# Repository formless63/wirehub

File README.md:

# WireHub

Capture the cable assemblies you build as one canonical definition, and get everything else
derived from it: schematic, build sheet, BOM, continuity spec and drawing. Self-hosted,
free software, deterministic output.

<p align="center">
  <picture>
    <source media="(prefers-color-scheme: dark)" srcset="docs/assets/hero-dark.webp">
    
  </picture>
</p>

<p align="center">
  <b><a href="https://formless63.github.io/wirehub/docs/">Documentation</a></b> ·
  <a href="https://formless63.github.io/wirehub/docs/quick-start/">Quick start</a> ·
  <a href="https://formless63.github.io/wirehub/generator/">Config generator</a> ·
  <a href="https://formless63.github.io/wirehub/store/">Module store</a>
</p>

## See it work

From a new design to a build sheet, about twenty seconds: the wizard wires what the catalog
states unambiguously, the canvas lets you change any joint, and every document follows.

## What you get

Every document is derived from the one definition, so they always agree.

<table>
  <tr>
    <td width="25%" valign="top"><br><sub><b>Schematic</b><br>laid out for you, with a legend and cross-section</sub></td>
    <td width="25%" valign="top"><br><sub><b>Build sheet</b><br>the bench flow, one stage per step</sub></td>
    <td width="25%" valign="top"><br><sub><b>Continuity spec</b><br>what must connect, what must stay isolated</sub></td>
    <td width="25%" valign="top"><br><sub><b>Drawing sheet</b><br>BOM, outline and title block on a framed sheet</sub></td>
  </tr>
</table>

Plus a BOM, formboard, wire labels, CSV and XLSX exports, and WireViz import and export.

## What is in it

- **A hierarchical wire model.** A stock is a tree: cables hold pairs, coax and cores,
  which hold conductors, shields and insulation. Bonded screens, drains, pigtails and
  breakouts (moulds where some conductors pass through and others end) are modelled
  as they are built.
- **A connector library.** A connector is a physical body (DE-9 male, XLR3 female)
  composed with a pinout (RS-232, balanced audio). Reuse one body for many pinouts.
- **PCBAs as black boxes** with declared internal continuity, so a trace runs through a
  board without modelling its electronics.
- **Derived, deterministic output.** Nets and traces, a continuity spec, a BOM, a
  bench build sheet, an ELK-laid-out SVG schematic and an ANSI-A drawing sheet all come
  from the same JSON definition, byte for byte the same every time.
- **An editor.** A React canvas for the wiring, a parts library with 3D views, a new-cable
  wizard, versions, edit locks and an optional login.
- **Modules.** Domain vocabularies (video, audio, fieldbus …) and what only one shop needs
  (its ERP link, its numbering scheme, its own importers) plug in at build time through
  a small registry instead of living in the base.

## Run it

You need Docker and one file — no clone, no `.env`:

```
mkdir wirehub && cd wirehub
curl -fsSLO https://raw.githubusercontent.com/formless63/wirehub/main/compose.yaml
docker compose up -d
docker compose logs wirehub        # the first-run setup code
```

Open <http://localhost:5183/setup>, enter the setup code and finish the short form; you land on a list of example designs to open. In a Docker UI
(Portainer, Komodo, Dockhand …), paste
[`compose.yaml`](https://raw.githubusercontent.com/formless63/wirehub/main/compose.yaml)
as a stack, deploy, and read the code from the `wirehub` container's logs.

On first start a one-shot `bootstrap` service generates every secret the stack
needs into a `secrets` volume and keeps it there. The few install choices — the
public URL, ports, backups (`COMPOSE_PROFILES=backup`), your own PostgreSQL or
S3 — go in an optional `.env`;
[`.env.example`](https://raw.githubusercontent.com/formless63/wirehub/main/.env.example)
explains each. Everything else — single sign-on, magic links, allowed emails,
alerts, the git mirror, job settings — is set in the app under **Settings** and
applies without a redeploy.

**Config generator: <https://formless63.github.io/wirehub/generator/>** — pick your
options and get a ready `compose.yaml` and `.env`. It runs entirely in your
browser and sends nothing anywhere.

**First-run setup** lists the bundled domain modules whose signals, connectors
and example cables you can add — **PC & serial** (RS-232, RS-485, USB),
**Networking** (RJ45, T568A/B), **Pro audio** (XLR, TRS, RCA), **AV / video** and
**Automotive** — all unticked unless the deployment suggests some. Nothing is
required, and more can be enabled later from the command palette. The base
itself stays generic: its starter catalog holds wire stocks, generic connectors
(DE-9 by pin number, JST XH, terminal blocks), parts and a few neutral example
cables.

The stack is the app, PostgreSQL 18 and [Garage](https://garagehq.deuxfleurs.fr/)
(S3-compatible storage for uploaded files), plus restic backups through
Backrest as an optional profile. `docs/self-hosting.md` has the details.

## Develop

From source (Node 24+, pnpm 10 — `corepack enable`):

```
git clone https://github.com/formless63/wirehub && cd wirehub
pnpm install
pnpm --filter studio dev        # open the printed URL
```

The hub opens on the generic starter catalog: a few example cables built from a
small library of generic parts, every value cited to a public standard or marked
as a synthetic example. The catalog is plain JSON under `packages/catalog/data`,
and saves go straight back to it; domain modules enabled at setup install their
packs into the gitignored `data/packs/`, so they never land in a commit to the
base.

```
pnpm build                      # tsc --noEmit, strict, every package
pnpm test                       # vitest, each workspace in turn
pnpm --filter @wirehub/model test -- test/trace.test.ts
bash scripts/privacy-check.sh --tree
```

`pnpm install` also enables git hooks that keep home paths, secrets and personal
emails out of commits (`CONTRIBUTING.md`).

| Package | |
| --- | --- |
| `@wirehub/model` | the canonical model: types, validation, nets, trace, part-number schemes. Zero dependencies. |
| `@wirehub/catalog` | the file-backed catalog and the starter data. Zero dependencies. |
| `@wirehub/modules` | the module API and build-time registry. Zero dependencies, MIT. |
| `@wirehub/layout` | ELK layout of a design |
| `@wirehub/render-svg` | deterministic SVG schematics and cross-sections |
| `@wirehub/docs` | build sheet, BOM, continuity spec, drawing, wire spec |
| `@wirehub/editor-react` | the editor |
| `apps/studio` | the app: Vite SPA and Hono server; `stack/` the compose stack's one-shots |
| `site` | the config generator, published to GitHub Pages |
| `modules/*` | bundled modules: optional domain modules (`pc-serial`, `networking`, `pro-audio`, `av-video`, `automotive`) and the always-on interop modules `wireviz` (WireViz YAML in and out) and `csv-library` (bulk CSV library import) |

## Read next

- **Documentation: <https://formless63.github.io/wirehub/docs/>** — quick start, your first design, concepts, and the reference below.
- `SPEC.md` — the model and the plan; the single source of truth.
- `docs/modules.md` — extension points, domain modules, and how a private module lives
  in its own repository.
- `docs/exports.md` — CSV/XLSX exports, the continuity tester export, wire labels, and rendering documents without a browser.
- `docs/interop.md` — WireViz YAML import and export, bulk CSV library import, and part costing.
- `docs/catalog-store.md` — catalog packs: format, provenance, install and update.
- `docs/store-hosting.md` — run your own module store from a GitHub template (or any static host).
- `docs/self-hosting.md` — install, the compose stack, secrets, storage, backups, development.
- `specs/postgres-backend.md` — the database backend (Phase A built).
- `docs/boundaries.md` — what this base was split from, and what it left out.

Contributing: `CONTRIBUTING.md` · Security: `SECURITY.md` · Conduct: `CODE_OF_CONDUCT.md`

## Licence

WireHub is free software under the **GNU Affero General Public License v3.0 only**
(`LICENSE`), with one additional permission, the **WireHub Module Exception**
(`MODULE-EXCEPTION.md`). In plain language:

- **WireHub itself stays open.** If you modify WireHub and run it for others — including
  over a network — you offer them the source of your modified WireHub, under the AGPL.
- **Modules can use any licence.** A module that talks to WireHub only through the module
  API (`@wirehub/modules`, the model and catalog types) and the catalog-pack formats may
  be MIT, proprietary, or anything else. You can build and distribute a WireHub image that
  includes it without the module becoming AGPL, and without publishing its source.
- **`@wirehub/modules` is MIT**, so module authors can depend on it freely.
- **Catalog data is CC0-1.0.** The starter catalog (`packages/catalog/data`) and the
  bundled modules' packs are dedicated to the public domain, so the facts in them can
  be reused anywhere. Other packs, and records in them, carry their own licence
  (`docs/catalog-store.md`).
- Third-party material keeps its own licence (`NOTICE`).

There are no per-file licence headers: `LICENSE`, `MODULE-EXCEPTION.md` and each
package's `license` field are the record (`SPDX: AGPL-3.0-only WITH
AdditionRef-WireHub-Module-Exception-1.0`, `packages/modules`: `MIT`; `packages/catalog`: `AGPL-3.0-only AND CC0-1.0`, the code and
its data; bundled modules: `MIT`, their packs `CC0-1.0`). This summary is
not legal advice; the licence texts govern.

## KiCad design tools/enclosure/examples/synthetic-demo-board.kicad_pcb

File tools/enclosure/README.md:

# Tool pack: enclosure

Parametric board enclosures with [build123d](https://github.com/gumyr/build123d) 0.13.0 on
Open CASCADE (OCP 8.0.1). Image `wirehub-tool-enclosure:0.3.5`; pins in `Dockerfile` and
`requirements.lock` (hash-checked, `uv pip compile requirements.in --generate-hashes`).

```sh
docker build -t wirehub-tool-enclosure:0.3.5 tools/enclosure
docker run --rm --network none --read-only --tmpfs /tmp \
  -v "$IN":/work/in:ro -v "$OUT":/work/out \
  wirehub-tool-enclosure:0.3.5 enclosure-generate /work/in/request.json
```

Same request, same bytes (0.3.3+): every STEP gets a fixed `FILE_NAME` stamp and a canonical
entity numbering (`repro.py`, the same file as `tools/kicad/repro.py`), and `result.json` /
`device-result.json` carry no timings (the run time is in `log.txt`).

## Op `enclosure-generate`

`request.json` → `params`:

- `boards[]`: `{ id, label, basis, thickness, outline: [[x, y], …], holes: [{ x, y, d }],
  components: [{ ref, x0, y0, x1, y1, height | null, basis?, side }], ports: [{ id, label, edge:
  front|back|left|right, at, z, width, height, shape: rect|round, protrude }], heightAbove,
  heightBelow }`. Board-local millimetres, **y toward the back**, origin at the outline's
  bounding-box minimum, underside at z = 0. `height: null` is an unknown height: it is modelled at
  `defaultComponentHeight` and reported, never treated as zero. A component whose `basis` is
  `estimated` (the studio read it from the footprint's name, not a 3D model) is reported as such
  and its collisions say so.
- `occurrences[]`: `{ id, board, x?, y?, rotation? }`. The same board may appear more than once;
  occurrences without `x`/`y` are laid out left to right.
- `enclosure`: design parameters (wall, floor, lid thickness, clearance, standoff height and
  diameter, pilot, lid `flat` with screw posts or `split` at a height, lip and fit, vents). All have
  defaults (`DEFAULTS` in `enclosure.py`).
- `openings[]`: extra cut-outs in the enclosure frame (`face`, `u`, `v`, `width`, `height`, `shape`).

Outputs (manifest roles): `base-step`, `lid-step`, `base-stl`, `lid-stl` (flipped plate-down for
printing), `assembly-step` (base, lid and board dummies), `preview-model` (`assembly.glb`, millimetres like the Library's own GLBs,
lid lifted), `preview-image` (`preview.png`, a z-buffered isometric render made without GL) and
`result` (`result.json`: outer/interior size, each occurrence's placement matrix, resolved
openings, supports, lid posts, volumes, the effective parameters). Each `supports[]` entry is
`{ occurrence, kind: board-hole | corner-pad, x, y, z }` (z = the support's top, the board's
underside; a `board-hole` also gives `holeDiameter`, `standoffDiameter`, `pilotDiameter`, a
`corner-pad` its `size`); each `lidPosts[]` entry is a flat lid's screw axis `{ x, y, size, z0, z1,
pilotDiameter, pilotDepth, screwZ }` (screwZ = the lid's outside), empty without lid screws.
Consumers read these instead of re-deriving them from the parameters.

Findings are advisory: unknown heights, ports set back from a wall, collisions between the
shell/lid and declared board geometry (boolean intersection, as in the reference generator),
missing mounting holes. Invalid parameters give `status: "failed"` with an `error` finding; the
process still exits 0. Running without `--user`, the pack hands its outputs to the owner of
`/work/out`.

Examples (synthetic and public-safe, made up for this pack): `examples/synthetic-two-boards.json`
is a request with one board placed twice; `examples/synthetic-demo-board.kicad_pcb` is a 60 × 40 mm
KiCad board built from KiCad's standard footprints by `examples/make-synthetic-board.py` (run with
KiCad's Python). Uploaded as a board's model in the Library, it gives an enclosure a native outline,
four mounting holes and two edge connectors.

In the app: a board's record → Enclosures → New enclosure creates a shell carrying the parameters;
its Enclosure panel saves them and runs Generate (`POST /api/enclosures/:id/generate`), an
`enclosure-generate` job run by the shared tool-pack runner where `WIREHUB_TOOL_RUNNER=docker` is set
(progress and Cancel in the panel; `docs/jobs-and-tool-packs.md`).

## Op `device-assemble` (pack 0.3.0)

A whole device in one run: `assemble.py` (the image's `entry.py` sends this op there). The studio
composes the device (`deviceScene` in `@wirehub/model`) and passes every placed thing as a part:
`{ path, kind, label, group?, matrix (4×4, device frame, mm, z up), provisional?, geometry }`, where
`geometry` is a STEP input (`frame: board` moves a KiCad board STEP so its PCB body's outline minimum
is the origin and its underside z = 0), a board outline with footprint boxes, a box, parametric
hardware (`screw`, `standoff`, `foot`) or a cable route tube. `params.drawing` fills the title block
and parts list (a long title wraps to two lines, then ends in an ellipsis; an unsaved-version export reads `unreleased`); `false` skips the sheet.

Outputs: `device-step` (device.step, one named, coloured node per part, grouped by sub-assembly),
`device-glb` (millimetres, y up), `preview-image`, `device-drawing` (an A3 SVG: front, top and right
views in third-angle projection with hidden lines, an isometric view, overall dimensions, parts list
and title block; lid screws and feet in a table with their pitch dimensioned), `device-drawing-pdf`
(that sheet plus one per nested sub-device, in its own frame with its own parts list: a multi-page
PDF; pack 0.3.3) and `result` (bounding box, each part's geometry and status, the sheet's scale).
Cable routes are in the STEP and GLB but not on the drawing: they are schematic. In the app: a
design's Device view → Exports (`POST /api/devices/:id/exports`, a `device-export` job), from the
working copy or the saved version being viewed.

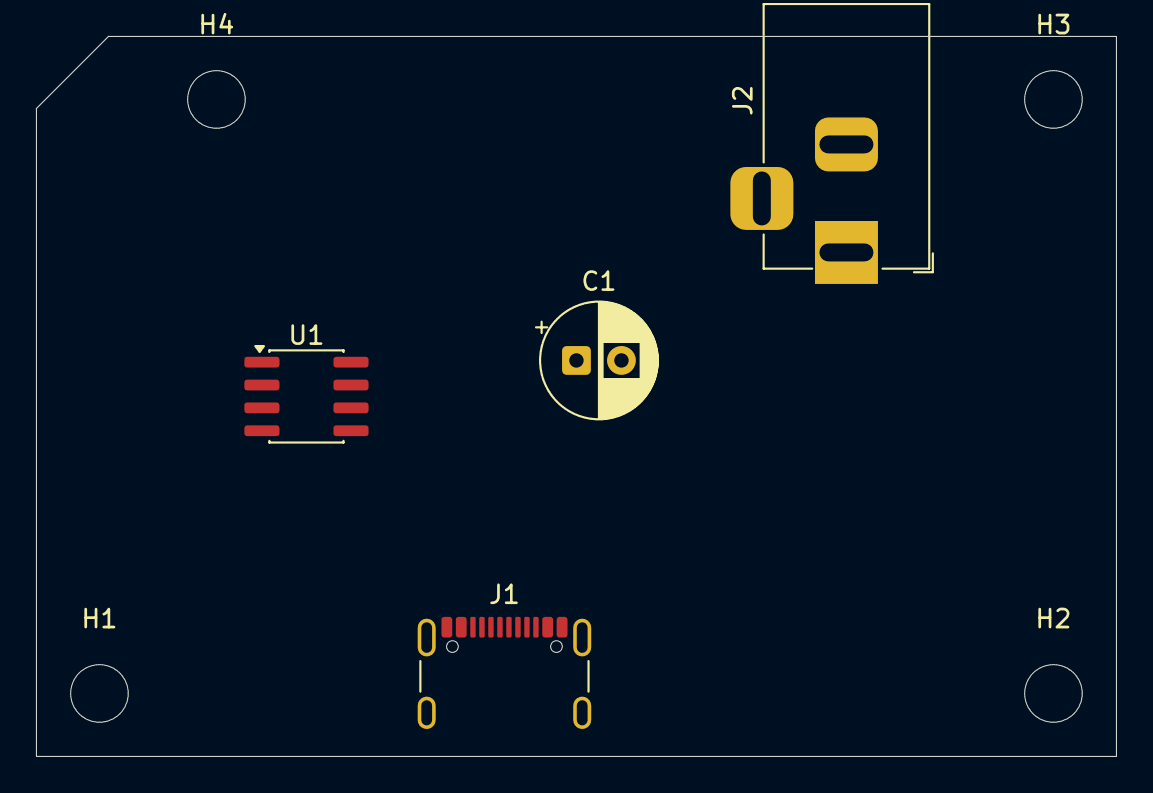
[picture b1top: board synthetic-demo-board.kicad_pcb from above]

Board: 2 copper layers, 60.0 x 40.0 mm, 8 parts (0 on the bottom side), 4 nets, no tracks yet.

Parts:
C1: 100uF; CP_Radial_D6.3mm_P2.50mm
H1, H2, H3, H4: MountingHole_3.2mm_M3
J1: USB-C; USB_C_Receptacle_GCT_USB4105-xx-A_16P_TopMnt_Horizontal
J2: DC 5.5/2.1; BarrelJack_Horizontal
U1: MCU; SOIC-8_3.9x4.9mm_P1.27mm

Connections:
/USB_D+: J1.A6, J1.B6, U1.2
/USB_D-: J1.A7, J1.B7, U1.3
GND: C1.2, J1.A1, J1.A12, J1.B1, J1.B12, J1.SH, J2.2, J2.3, U1.4
VBUS: C1.1, J1.A4, J1.A9, J1.B4, J1.B9, J2.1, U1.8
